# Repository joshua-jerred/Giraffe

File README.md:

# Giraffe <!-- omit from toc -->

### A Unified Flight Command and Control System <!-- omit from toc -->

### [Iteration 0.8](https://giraffe.joshuajer.red/md_docs_Doxygen_pages_versions.html)

---

## Learn More About it

Read about why I'm doing this: [https://joshuajer.red/Giraffe-Introduction/](https://joshuajer.red/Giraffe-Introduction/)

Detailed software documentation (Doxygen): [http://giraffe.joshuajer.red/](http://giraffe.joshuajer.red/)

Check out the [Giraffe GitHub Project](https://github.com/users/joshua-jerred/projects/3) to see what I'm currently working on.

---

## Photos

> 
> The Giraffe Network - A diagram of Giraffe's components and how they interact with each other.

> 
> The web client 'command center' page.

> 
>
> The flight computer prototype 2 PCB on top of a Pi 4. It's accompanied by the SA868 testing PCB with a dummy load antenna and it's supporting PCM2902 sound card testing PCB. Connected with debugging spaghetti.

>  >
> This is the web client, used to configure the flight computer on the ground
> and to monitor/control it in the air.

---

## Table of Contents <!-- omit from toc -->

- [About](#about)
  - [Current High Level Functionality](#current-high-level-functionality)
  - [Planned High Level Functionality Prior to the First Flight](#planned-high-level-functionality-prior-to-the-first-flight)
  - [Development Details](#development-details)
- [Hardware](#hardware)
  - [Hat](#hat)
  - [Shoe](#shoe)
- [Building and Installing the Flight Software](#building-and-installing-the-flight-software)
  - [Installing Prerequisites](#installing-prerequisites)
  - [Building the Flight Software](#building-the-flight-software)
- [Flight Software Configuration/Web Client](#flight-software-configurationweb-client)

---

# About

Giraffe is a "flight command and control system" first developed for high
altitude balloon flights.

The purpose of this project is mainly to have a 'learning lab' where I can experiment with all of the things that I'm interested in. This includes C++, Linux Embedded Development, Circuit Design, RF/Amateur Radio, Node.js, CI, interfacing hardware with the web, meta-programming, and more.

The system includes the following key components:

- **GFS** Giraffe Flight System
  - The hardware and software that actually flies
- **GGS** Giraffe Ground Station
  - Software that helps interface with the flight system both on the ground
    and in the air.
- **GDL** Giraffe Data Link
  - The hardware and software used on both GFS and GGS to connect them together
    via long distance radio links.
- **GWC** Giraffe Web Client
  - A web client to easily configure, control, and monitor all Giraffe
    components in one place.

## Current High Level Functionality

- Detailed configuration via the web interface of all system components.
- Telemetry support for APRS, SSTV, and Data Packets.
- Aggressive error handling for all software components. Everything is designed
  to be able to fail gracefully and recover when possible.
- Detailed and configurable logging of data and telemetry.
- Drivers/Firmware for the Raspberry Pi BCM interface along with many different sensors, radios, and other hardware.

## Planned High Level Functionality Prior to the First Flight

- Two way communication via GDL

## Development Details

The flight software is written in C++, the web interface and ground stations are written in Node.js, and some Python is sprinkled in.

There are common components, including a large collection of configuration
and data point metadata files that are used to generate code for both the
flight system and the ground station. For example, to add a configuration
option for the flight computer, you just need to add the information to the
metadata file, run the generator, rebuild, and redeploy. It will then be inside
of the flight software, configurable via the web interface, and safely
implemented to restrained values to prevent misconfiguration.
This works for integers, floats, strings, and enums.

Being a 'learning lab' project, nearly everything is built from the ground up
including my own implementations of:

- Linux I2C and Serial wrappers
- BCM Interface for direct GPIO control on the Raspberry Pi
- Device Drivers
  - BMP180 (I2C Environmental Sensor)
  - BME280 (I2C Environmental Sensor)
  - SAM-M8Q (I2C GPS using the UBX protocol)
  - SA868 (2w VHF Radio Module)
  - MCP3021 (I2C ADC)
- Modulation (Using my WAV file generation and Modulation library)
  - PSK - For data packets
  - AFSK, AX.25, APRS (Position and Telemetry) - For tracking via aprs.fi
  - SSTV (Robot36) - For image transmission
- A web interface for flight computer debugging, configuration, and control
- Custom hardware for the flight computer
- Simple configuration file for the flight computer

Libraries that I've written for this project:

- [Boost_erSeat, a library with a few useful functions that I use in many different projects](https://github.com/joshua-jerred/Boost_erSeat)
- [WavGen, a .wav File Generator](https://github.com/joshua-jerred/WavGen)
- [MWAV, a library for modulating AFSK, AX.25, APRS, PSK31, and SSTV signals using WavGen](https://github.com/joshua-jerred/MWAV)
- [SSTV Image Tools, a library for overlaying text and getting pixel data for SSTV images](https://github.com/joshua-jerred/SSTV-Image-Tools)

Where I used existing 3rd party libraries:

- JSON parsing for the web server module and configuration reading (nlohmann/json)
- Image Manipulation for PNG/JPEG support in my SSTV Image Tools Library (Magick++)
- Google Test for unit testing

Everything is designed to be modular and extensible so that it can be used for
all types of HAB flights or even some other future implementations where command
and control is needed. The software is made to work on any ARM based single
board computer that runs Linux, like the Raspberry Pi but it is targeted towards
the Pi Zero 2 and Pi 4.

The framework utilizes open communication protocols/modulation modes like APRS,
AFSK, PSK31, and SSTV to allow for easy integration into existing software. Two
way communication, which is currently in development, allows you to send
commands to the flight computer from the ground station. There is a lot more
included that isn't mentioned here, so please see the
[rest of the documentation](http://giraffe.joshuajer.red/).

Too see my more older, simplified, python implementation of this
project check out the [the AOS repo.](https://github.com/joshua-jerred/AOS)

---

# Hardware

I'm currently working on hardware prototypes.

The flight computer is (will be) made up of two boards; it is targeted towards the
Raspberry Pi Zero 2 and maintains the same footprint. The Raspberry Pi will
be sandwiched between the two boards, with the top board being the "hat" and
the bottom board being the "shoe".

## Hat

The hat contains the majority of the circuitry. It is a four layer PCB
containing the following:

- Power Management
  - Connects to the battery (21700 Cells) via a terminal block
  - Includes a 5v linear regulator and support circuitry, this powers the Pi and
    the other PCB
  - Voltage Divider for battery voltage measurement
- Sensors
  - BME280 (Temperature, Pressure, Humidity)
  - MCP3021 (Battery Voltage)
  - CAT24C32 (EEPROM, GPIO Configuration at boot)
  - BMI088 (6 Axis IMU)
- 2x 1-Wire Headers for DS18B20 Temperature Sensors
- 1x I2C Header for general expansion

>  >

> You'll notice a lot of open space on the top of the PCB, this is to isolate
> the SAM-M8Q and to provide it a large ground plane. Although the ground plane
> size is out of spec I have had no issues with acquiring and maintaining a GPS
> lock.

### Known Issues <!-- omit in toc -->

There are a few known issues with prototype 2:

- Power Management! I'm currently working on replacing the linear regulator with
  a boost converter.
- The BME280 is too close to the power supply. This results in much higher
  temperature readings and inaccurate pressure/humidity readings as they're
  temperature compensated.

Other than that, this prototype is working great!

## Shoe

The shoe contains the telemetry circuitry. It is a four layer PCB containing
the following:

- SA868 (2w VHF Radio)
  - Isolation circuitry to prevent interference with the Pi
  - Serial Logic Level Converter (3.3v to 5v)
- Low Pass Filter and SMA Connector
- Integrated PCM2902 Audio Codes
  - USB interface with the Pi
  - 2x input channels, 2x output channels, only one of each is currently used.
- An attempt to impedance match the RF traces from the SA868 to the
  SMA connector and provide shielding.

The radio will be on the very bottom of the hardware stack, hopefully isolating
it from the rest of the hardware.

> Front 

> Back 

### Known Issues <!-- omit in toc -->

- Power control circuitry is not functional. Although 5v power is fully cut off
  with the GPIO controlled optical relay, the SA868 still draw power from
  the serial logic level converter. This results is the SA868 being unreliable
  after restarts and frequency changes. More isolation needs to be added.

### Shoe Testing PCBs <!-- omit in toc -->

I'm just waiting to finish debugging the SA868 and PCM2902 testing PCBs before
ordering this one.

> <p float="left">
> 
> 
> </p>
> Left: SA868 Testing PCB with a dummy load antenna.
>
> Right: PCM2902 Testing PCB with USB interface.

> 
>
> Unfortunately, I don't have the equipment to test it properly, but the SA868
> PCB includes a low pass filter to take care of the messy RF output that these
> modules are known to have.

---

# Building and Installing the Flight Software

## Installing Prerequisites

## Building the Flight Software

```bash
# Clone the repo with it's submodules (MWAV, WAVGen, and SSTV Image Tools)
git clone --recurse-submodules https://github.com/joshua-jerred/Giraffe.git

# If using the --recurse-submodules flag didn't work for any reason, you can use:
# git submodule update --init --recursive --remote
# and then pull the latest change.

# Move into the repo and create a build directory
cd Giraffe && mkdir build && cd build

# Configure the build
cmake .. # You can add -DSSTV_ENABLED=OFF to disable SSTV (Requires Magick++)

# Build the flight system
make giraffe_flight_system

# Install is currently disabled until some details are finalized
# Install the flight system (Optional)
# sudo make install
```

---

# Flight Software Configuration/Web Client

Configuration is no longer done through the config file, but instead through
the web interface! This is where the ground station and flight system are
configured.

Multiple clients can be connected to the web interface at once to allow for a
team to monitor the flight together.

---

Development is no longer done by release, but instead features will be added
as they are completed.

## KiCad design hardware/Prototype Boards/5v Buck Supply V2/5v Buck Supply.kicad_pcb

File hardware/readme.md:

# Giraffe Hardware

- KiCad 7+
- All symbols should be in the `./symbols/` directory
- All footprints should be in the `./footprints/` directory

Slowly moving to a more modular design and better documentation.

## Flight Computer
- ./giraffe_flight_computer/
- ./power_board/

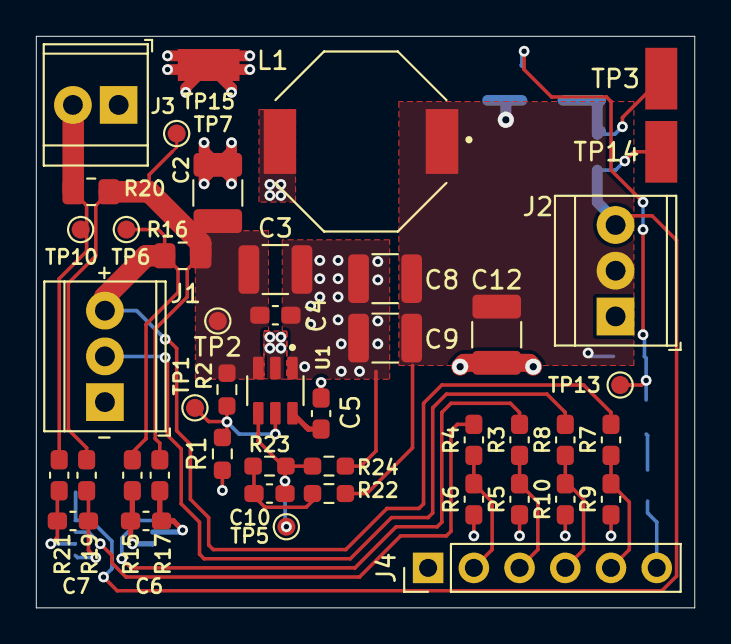
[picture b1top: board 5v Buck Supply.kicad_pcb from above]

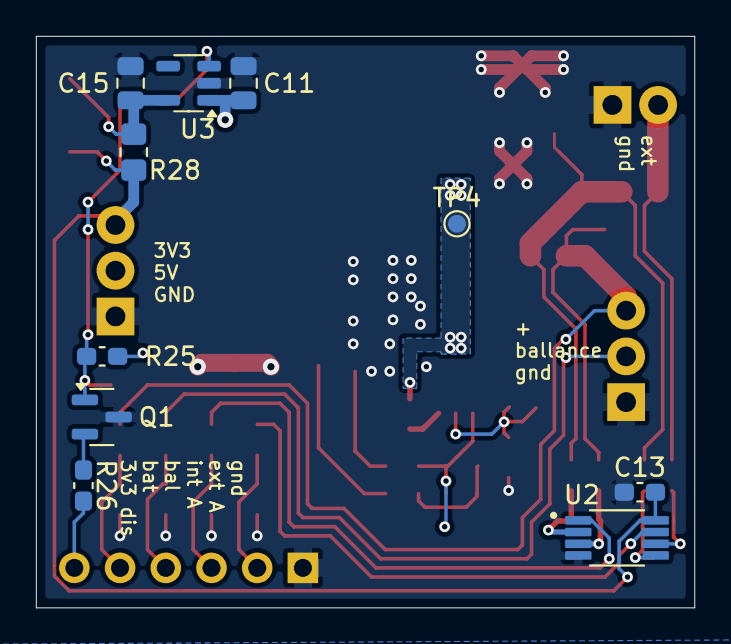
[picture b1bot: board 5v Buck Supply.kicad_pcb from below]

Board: 2 copper layers, 36.6 x 31.8 mm, 55 parts (10 on the bottom side), 26 nets.

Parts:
C2, C12: DNS; C_1210_3225Metric_Pad1.33x2.70mm_HandSolder
C3: 10uf; C_1210_3225Metric
C4, C5, C13: 0.1uf; C_0603_1608Metric_Pad1.08x0.95mm_HandSolder
C6, C7: DNS; C_0603_1608Metric_Pad1.08x0.95mm_HandSolder
C8, C9: 22uf; C_1210_3225Metric
C10: 75pf; C_0603_1608Metric_Pad1.08x0.95mm_HandSolder
C11, C15: 1uf; C_0805_2012Metric
J1: BATT; TerminalBlock_TE_282834-3_1x03_P2.54mm_Horizontal
J2: PRIMARY; TerminalBlock_TE_282834-3_1x03_P2.54mm_Horizontal
J3: EXTERNAL; TerminalBlock_TE_282834-2_1x02_P2.54mm_Horizontal
J4: IO; PinHeader_1x06_P2.54mm_Vertical
L1: 10uH; IND_SRU1048-100Y
Q1: NPN; SOT-23
R1, R2: DNS; R_0603_1608Metric_Pad0.98x0.95mm_HandSolder
R3, R4, R5, R6, R7, R8, R9, R10, R25, R26: R; C_0603_1608Metric_Pad1.08x0.95mm_HandSolder
R15, R17, R19, R21: 0; C_0603_1608Metric_Pad1.08x0.95mm_HandSolder
R16, R20, R28: R; R_0805_2012Metric_Pad1.20x1.40mm_HandSolder
R22: 49.9k; R_0603_1608Metric_Pad0.98x0.95mm_HandSolder
R23: 100k; R_0603_1608Metric_Pad0.98x0.95mm_HandSolder
R24: 13.3k; R_0603_1608Metric_Pad0.98x0.95mm_HandSolder
TP1, TP6, TP7, TP10: TestPoint; TestPoint_Pad_D1.0mm
TP2, TP4, TP5, TP13: TestPoint_Pad_D1.0mm
TP3, TP14, TP15: TestPoint; KEYSTONE_5015
U1: TPS54302DDCR; SOT95P280X110-6N
U2: INA2180Ax; SOP65P490X110-8N
U3: AP2112K-3.3; SOT-23-5

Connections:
3V3 Primary: C13.1, J2.3, R28.2, TP14.1, U2.8 (VS)
3V3_DISABLE: J4.6, R26.2
5V Primary: C8.1, C9.1, C11.1, C12.1, J2.2, L1.1, R22.1, R25.2, U3.1 (VIN)
+BATT: J1.3, R7.1, R15.1, R16.1, TP6.1
+BATT External: J3.2, R20.2, R21.1, TP10.1
+BATT Primary: C2.1, C3.1, C4.1, R2.2, R16.2, R17.1, R19.1, R20.1, TP2.1, TP7.1, U1.3 (VIN)
/3v3_en: Q1.1 (C), R25.1, TP13.1, U3.3 (EN)
/3v3_out: C15.1, R28.1, TP3.1, U3.5 (VOUT)
/adc_scaled:batt: J4.5, R7.2, R9.1
/adc_scaled:batt_ballance: J4.4, R8.2, R10.1
/adc_scaled:current_batt: J4.3, R3.2, R5.1
/adc_scaled:current_external: J4.2, R4.2, R6.1
/batt_ext+: C7.2, R19.2, U2.5 (IN+2)
/batt_ext-: C7.1, R21.2, U2.6 (IN-2)
/batt_primary+: C6.2, R15.2, U2.3 (IN+1)
/batt_primary-: C6.1, R17.2, U2.2 (IN-1)
/buck_boot: C5.1, U1.6 (BOOT)
/buck_enable: R1.2, R2.1, TP1.1, U1.5 (EN)
/buck_feedback: C10.2, R23.2, R24.1, TP5.1, U1.4 (FB)
/buck_sw: C5.2, L1.2, TP4.1, U1.2 (SW)
GND: C2.2, C3.2, C4.2, C8.2, C9.2, C11.2, C12.2, C13.2, C15.2, J1.1, J2.1, J3.1, J4.1, Q1.3 (E), R1.1, R5.2, R6.2, R9.2, R10.2, R24.2, TP15.1, U1.1 (GND), U2.4 (GND), U3.2 (GND)
unnamed: C10.1, R22.2, R23.1
unnamed: Q1.2 (B), R26.1
batt_ballance: J1.2, R8.1
current_sense_batt: R3.1, U2.1 (OUT1)
current_sense_external: R4.1, U2.7 (OUT2)

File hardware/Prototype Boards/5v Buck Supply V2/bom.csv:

"Reference","Value","Footprint","Qty","DNP"
"BAT_CON1","BAT","","1","DNP"
"C2,C12,R1,R2","DNS","-- mixed values --","4","DNP"
"C3","10uf","Capacitor_SMD:C_1210_3225Metric","1",""
"C4,C5,C13","0.1uf","Capacitor_SMD:C_0603_1608Metric_Pad1.08x0.95mm_HandSolder","3",""
"C6,C7","C","Capacitor_SMD:C_0603_1608Metric_Pad1.08x0.95mm_HandSolder","2",""
"C8,C9","22uf","Capacitor_SMD:C_1210_3225Metric","2",""
"C10","75pf","Capacitor_SMD:C_0603_1608Metric_Pad1.08x0.95mm_HandSolder","1",""
"C11,C15","1uf","Capacitor_SMD:C_0805_2012Metric","2",""
"J1","BATT","TerminalBlock_TE-Connectivity:TerminalBlock_TE_282834-3_1x03_P2.54mm_Horizontal","1",""
"J2","PRIMARY","TerminalBlock_TE-Connectivity:TerminalBlock_TE_282834-3_1x03_P2.54mm_Horizontal","1",""
"J3","EXTERNAL","TerminalBlock_TE-Connectivity:TerminalBlock_TE_282834-2_1x02_P2.54mm_Horizontal","1",""
"J4","IO","Connector_PinHeader_2.54mm:PinHeader_1x06_P2.54mm_Vertical","1",""
"L1","10uH","footprints:IND_SRU1048-100Y","1",""
"Q1","NPN","Package_TO_SOT_SMD:SOT-23","1",""
"R3,R4,R5,R6,R7,R8,R9,R10,R15,R16,R17,R19,R20,R21,R25,R26,R28","R","-- mixed values --","17",""
"R22","49.9k","Resistor_SMD:R_0603_1608Metric_Pad0.98x0.95mm_HandSolder","1",""
"R23","100k","Resistor_SMD:R_0603_1608Metric_Pad0.98x0.95mm_HandSolder","1",""
"R24","13.3k","Resistor_SMD:R_0603_1608Metric_Pad0.98x0.95mm_HandSolder","1",""
"TP1,TP3,TP6,TP7,TP10,TP14,TP15","TestPoint","-- mixed values --","7",""
"TP2,TP4,TP5,TP13","~","TestPoint:TestPoint_Pad_D1.0mm","4",""
"U1","TPS54302DDCR","footprints:SOT95P280X110-6N","1",""
"U2","INA2180Ax","footprints:SOP65P490X110-8N","1",""
"U3","AP2112K-3.3","Package_TO_SOT_SMD:SOT-23-5","1",""

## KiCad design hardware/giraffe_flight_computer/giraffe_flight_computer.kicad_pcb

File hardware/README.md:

Currently in the prototyping stage, nothing here should be used as reference.

Some footprints are from SnapEDA so they could not be included due to license restrictions.

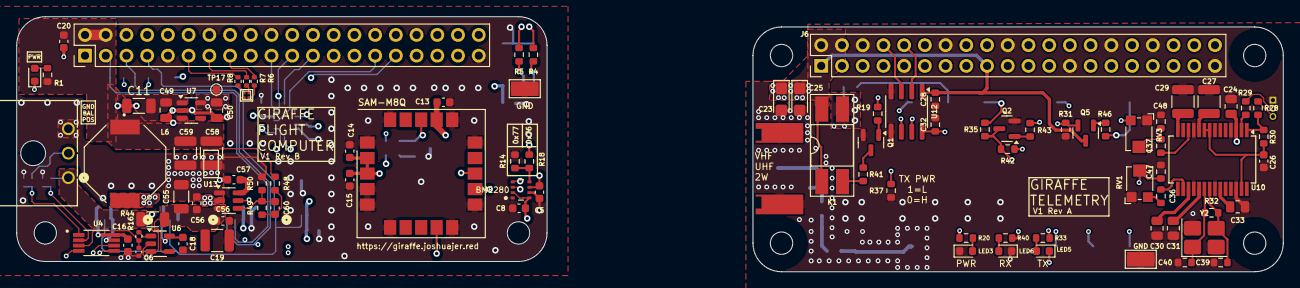
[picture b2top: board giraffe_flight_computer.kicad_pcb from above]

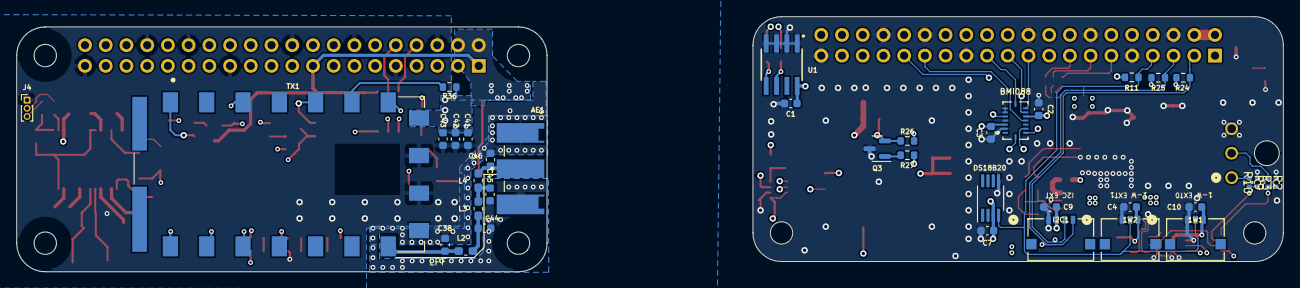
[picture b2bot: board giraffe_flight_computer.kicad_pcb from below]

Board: 4 copper layers, 155.2 x 31.3 mm, 129 parts (37 on the bottom side), 84 nets.

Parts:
1W1: 1W1; CONN_5037630000-SD_03_MOL
1W2: 1W2; CONN_5037630000-SD_03_MOL
AE1: ANT; MolexSmaConnector
C1, C2, C3, C4, C5, C7, C8, C9, C10, C13, C14, C15, C16, C18, C20, C41, C56, C56#2, C57: 0.1µF; C_0603_1608Metric
C6: C_Small; C_0402_1005Metric
C11: 10uf; C_1206_3216Metric
C19, C58, C59: 22µF; C_1210_3225Metric
C23, C25: 10μF; CP_EIA-3216-18_Kemet-A
C24, C31, C33: 1μF; R_0805_2012Metric
C26: 1μF; C_0603_1608Metric
C27, C29: 10μF; R_1210_3225Metric
C28, C32, C39, C40: 0.1μF; R_0603_1608Metric
C30: 1uF; R_0805_2012Metric
C36, C37: 1μF; R_0603_1608Metric
C38, C46: 20pF; C_0603_1608Metric
C42: 10kpF; C_0603_1608Metric
C43: 1kpF; C_0603_1608Metric
C44, C45: 36pF; C_0603_1608Metric
C47, C48: ?; R_0603_1608Metric
C49, C50: 1uf; C_0805_2012Metric
C55: 10µF; C_1206_3216Metric
C60: 75pf; C_0603_1608Metric
GND: GND; TestPoint_Keystone_5015_Micro-Minature
I2C1: I²C; CONN_5037630000-SD_04_MOL
J1: PI; pi_zero
J4: USB; PinHeader_1x03_P1.00mm_Vertical
J6: PI; SHOE_PCB
J7: Conn_01x03; CONN_SD-43650-001_03_MOL
K1: TLP241A; DIP-4_W8.89mm_SMDSocket_LongPads
L2, L4: 56nH; L_0603_1608Metric_Pad1.05x0.95mm_HandSolder
L3: 68nH; L_0603_1608Metric_Pad1.05x0.95mm_HandSolder
L6: 10uH; IND_SRU1048-100Y
LED1: SML-D12M8WT86; LED_0603_1608Metric
LED2: B36S3RGB-F6C0001HOU1930; B36S3RGB LED
LED3: PWR; LED_0603_1608Metric
LED5, LED6: LED_0603_1608Metric
Q1, Q2, Q5: BC847CT; SOT-23
Q3: NPN; SOT-23
R1: 56Ω; R_0603_1608Metric
R2, R3: ?; R_0402_1005Metric
R4, R5: 3.9kΩ; R_0603_1608Metric
R6: 270Ω; R_0402_1005Metric
R7, R8: 360Ω; R_0402_1005Metric
R9: 6.8k; R_0402_1005Metric
R10: 2.2k; R_0402_1005Metric
R11: 4.7kΩ; R_0603_1608Metric
R14, R18, R35, R36, R37: 0Ω; R_0603_1608Metric
R16: R_Small; R_0402_1005Metric
R19, R43: 50kΩ; R_0603_1608Metric
R20, R33: 150Ω; R_0603_1608Metric
R24, R25: *; R_0603_1608Metric
R26, R27: ?Ω; R_0603_1608Metric
R28, R29: 22Ω; R_0603_1608Metric
R30: 1.5kΩ; R_0603_1608Metric
R31, R42, R46: 5kΩ; R_0603_1608Metric
R32: 1MΩ; R_0603_1608Metric
R40: ?kΩ; R_0603_1608Metric
R41: 470Ω; R_0603_1608Metric
R44: 0.01Ω; R_1206_3216Metric
R48: 49; R_0603_1608Metric
R49: 100k; R_0603_1608Metric
R50: 13.3k; R_0603_1608Metric
RV1, RV3: 100k; Potentiometer_Bourns_TC33X_Vertical
TP3: GND; TestPoint_Keystone_5015_Micro-Minature
TP17: TestPoint; TestPoint_Pad_D1.0mm
TX1: SA868; DORJI_DRA818V
U1: CAT24C32; CAT24C32WI_GT3
U2: BMI088
U3: DS18B20; MSOP-8_3x3mm_P0.65mm
U4: MAX11613; SOP65P490X110-8N
U5: BME280
U6: INA180A3; SOT-23-5
U7: TLV75533PDBV; SOT-23-5
U8: SAM-M8Q; ublox_SAM-M8Q
U10: PCM2902C; SSOP-28_5.3x10.2mm_P0.65mm
U12: ISO6720B; SOIC-8_3.9x4.9mm_P1.27mm
U13: TPS54302; SOT-23-6
Y2: 12 MHz; Crystal_SMD_3225-4Pin_3.2x2.5mm_HandSoldering

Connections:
/hat/1_WIRE: 1W1.2, 1W2.2, J1.7 (GCLK0/GPIO4), R11.2, U3.4 (DQ)
/hat/+BATT: J7.1, R9.1, R44.1, U6.3 (+)
/hat/ADC.CH0: R2.2, R3.1, U4.1 (AIN0)
/hat/ADC.CH1: R9.2, R10.1, U4.2 (AIN1)
/hat/ADC.CH2: C6.1, R16.2, U4.3 (AIN2)
/hat/BAT_BALANCE: J7.2, R2.1
/hat/BAT_SENSED: C19.1, C55.1, C56.1, C56#2.1, R44.2, U6.4 (-), U13.3 (VIN)
/hat/BMI088.INT1: J1.31 (GCLK2/GPIO6), U2.16 (INT1)
/hat/BMI088.INT3: J1.29 (GCLK1/GPIO5), U2.12 (INT3)
/hat/EEPROM.SCL: J1.28 (ID_SC/GPIO1), R5.1, U1.6 (SCL)
/hat/EEPROM.SDA: J1.27 (ID_SD/GPIO0), R4.1, U1.5 (SDA)
/hat/I2C0.SCL: I2C1.4, J1.5 (SCL/GPIO3), R25.2, U4.5 (SCL), U5.4 (SCK), U8.12 (SCL)
/hat/I2C0.SDA: I2C1.3, J1.3 (SDA/GPIO2), R24.1, U4.6 (SDA), U5.3 (SDI), U8.9 (SDA)
/hat/SAM_M8Q.RST: J1.32 (PWM0/GPIO12), R27.2
/hat/SAM_M8Q.TX_RDY: J1.33 (PWM1/GPIO13), U8.13 (TXD)
/hat/SPI0.CE0: J1.24 (~CE0/GPIO8), U2.14 (CSB1)
/hat/SPI0.CE1: J1.26 (~CE1/GPIO7), U2.5 (CSB2)
/hat/SPI0.MISO: J1.21 (MISO0/GPIO9), U2.10 (SDO2), U2.15 (SDO1)
/hat/SPI0.MOSI: J1.19 (MOSI0/GPIO10), U2.9 (SDA/SDI)
/hat/SPI0.SCLK: J1.23 (SCLK0/GPIO11), U2.8 (SCL/SCK)
/hat/STATUS_LED.BLUE: J1.11 (GPIO17), R8.1
/hat/STATUS_LED.GREEN: J1.13 (GPIO27), R7.1
/hat/STATUS_LED.RED: J1.15 (GPIO22), R6.1
/shoe/AUDIO_IN_LEFT: C37.2, C48.1, RV3.2
/shoe/PI_GPIO_SA868_PTT: J6.18 (GPIO24), R43.1
/shoe/PI_GPIO_SA868_RX: J6.22 (GPIO25), Q5.2 (E), R31.1, R40.2
/shoe/PI_GPIO_SHOE_POWER_CONTROL: J6.16 (GPIO23), R19.1
/shoe/SA868 AUDIO_OUT: RV3.3, TX1.3 (AF_OUT)
/shoe/SA868 H/L: R37.2, TX1.7 (H/L)
/shoe/SA868 MIC_IN: C47.1, RV1.2, TX1.18 (MIC_IN)
/shoe/SA868 PTT: R35.2, TX1.5 (PTT)
/shoe/SA868 RF: C38.1, L2.1, TX1.12 (ANT)
/shoe/SA868 RX: R46.1, TX1.1 (SQ)
/shoe/SA868 UART RXD: TX1.16 (RXD), U12.6 (OUTB)
/shoe/SA868 UART TXD: TX1.17 (TXD), U12.7 (INA)
/shoe/S_5V_IN: C23.1, C25.1, J6.2 (5V), J6.4 (5V), K1.1 (Anode), K1.4 (Drain)
/shoe/UART.RX: J6.10 (GPIO15/RXD), U12.2 (OUTA)
/shoe/UART.TX: J6.8 (GPIO14/TXD), U12.3 (INB)
/shoe/USB Audio Codec/audio_codec_out_left: C36.2, RV1.3
H_3V3: 1W1.3, 1W2.3, C1.1, C2.2, C3.2, C4.2, C5.2, C7.2, C8.2, C9.2, C10.2, C13.1, C14.1, C15.1, C16.1, C18.1, C50.2, I2C1.2, R4.2, R5.2, R11.1, R18.2, R24.2, R25.1, R26.2, TP17.1, U1.8 (VCC), U2.3 (VDD), U2.11 (VDDIO), U3.3 (V_{DD}), U4.8 (Vdd), U5.2 (CSB), U5.6 (VDDIO), U5.8 (VDD), U6.5 (V+), U7.5 (OUT), U8.2 (VCC_IO), U8.3 (V_BCKP), U8.17 (VCC)
H_5V: C11.2, C20.2, C49.2, C58.1, C59.1, J1.2 (5V), J1.4 (5V), L6.1, R1.1, R48.1, U7.1 (IN), U7.3 (EN)
H_GND: 1W1.1, 1W2.1, C1.2, C2.1, C3.1, C4.1, C5.1, C6.2, C7.1, C8.1, C9.1, C10.1, C11.1, C13.2, C14.2, C15.2, C16.2, C18.2, C19.2, C20.1, C49.1, C50.1, C55.2, C56.2, C56#2.2, C58.2, C59.2, I2C1.1, J1.6 (GND), J1.9 (GND), J1.14 (GND), J1.20 (GND), J1.25 (GND), J1.30 (GND), J1.34 (GND), J1.39 (GND), J7.3, LED1.1 (K), LED2.4 (K), Q3.3 (E), R3.2, R10.2, R14.2, R50.2, TP3.1, U1.1 (A0), U1.2 (A1), U1.3 (A2), U1.4 (VSS), U2.2 (NC), U2.4 (GNDA), U2.6 (GNDIO), U2.7 (PS), U3.5 (GND), U4.7 (GND), U5.1 (GND), U5.7 (GND), U6.2 (GND), U7.2 (GND), U8.1 (GND), U8.4 (GND), U8.5 (GND), U8.6 (GND), U8.10 (GND), U8.11 (GND), U8.15 (GND), U8.16 (GND), U8.20 (GND), U13.1 (GND)
unnamed: AE1.1 (A), C46.1, L4.2
unnamed: C44.1, L2.2, L3.1
unnamed: C45.1, L3.2, L4.1
unnamed: C60.1, R48.2, R49.1
unnamed: J4.2, R29.1
unnamed: J4.3, R28.1
unnamed: K1.2 (Cathode), R41.1
unnamed: LED1.2 (A), R1.2
unnamed: LED2.3 (BA), R8.2
unnamed: LED2.2 (GA), R7.2
unnamed: LED2.1 (RA), R6.2
unnamed: LED3.2 (A), R20.2
unnamed: LED5.2 (A), R33.1
unnamed: LED5.1 (K), Q2.3 (C), R35.1, R42.2
unnamed: LED6.2 (A), R40.1
unnamed: Q1.1 (B), R19.2
unnamed: Q1.3 (C), R41.2
unnamed: Q2.1 (B), R43.2
unnamed: Q3.1 (B), R27.1
unnamed: Q3.2 (C), R26.1, U8.18 (~RESET)
unnamed: Q5.1 (B), R46.2
unnamed: R16.1, U6.1
unnamed: R36.1, TX1.6 (PD)
unnamed: R14.1, R18.1, U5.5 (SDO)
unnamed: R28.2, R30.2, U10.1 (D+)
unnamed: R29.2, U10.2 (D-)
unnamed: C26.2, R30.1, U10.8 (SEL0), U10.9 (SEL1), U10.27 (VDDI)
unnamed: C27.1, U10.10 (VCCCI)
unnamed: C30.2, U10.17 (VCCP1I)
unnamed: C31.2, U10.19 (VCCP2I)
unnamed: C33.2, U10.23 (VCCXI)
unnamed: C29.1, U10.14 (VCOM)
unnamed: C37.1, U10.12 (VINL)
unnamed: C36.1, U10.16 (VOUTL)
unnamed: C39.1, R32.2, U10.21 (XTI), Y2.3
unnamed: C40.1, R32.1, U10.20 (XTO), Y2.1
unnamed: C57.1, U13.6 (BOOT)
unnamed: C60.2, R49.2, R50.1, U13.4 (FB)
unnamed: C57.2, L6.2, U13.2 (SW)
S_3V3: C28.2, J6.1 (3V3), J6.17 (3V3), Q5.3 (C), U12.1 (VCC1)
S_5V: C24.1, C32.1, C41.2, C42.2, C43.2, K1.3 (Drain), R20.1, R33.2, R36.2, R42.1, TX1.8 (VBAT), U10.3 (VBUS), U12.8 (VCC2)
S_GND: AE1.2 (Shield), AE1.3 (Shield), AE1.4 (Shield), AE1.5 (Shield), C23.2, C24.2, C25.2, C26.1, C27.2, C28.1, C29.2, C30.1, C31.1, C32.2, C33.1, C38.2, C39.2, C40.2, C41.1, C42.1, C43.1, C44.2, C45.2, C46.2, C47.2, C48.2, GND.1, J4.1, J6.6 (GND), J6.9 (GND), J6.14 (GND), J6.20 (GND), J6.25 (GND), J6.30 (GND), J6.34 (GND), J6.39 (GND), LED3.1 (K), LED6.1 (K), Q1.2 (E), Q2.2 (E), R31.2, R37.1, RV1.1, RV3.1, TX1.9 (GND), TX1.10 (GND), U10.4 (DGNDU), U10.11 (AGNDC), U10.18 (AGNDP), U10.22 (AGNDX), U10.26 (DGND), U12.4 (GND1), U12.5 (GND2), Y2.2, Y2.4

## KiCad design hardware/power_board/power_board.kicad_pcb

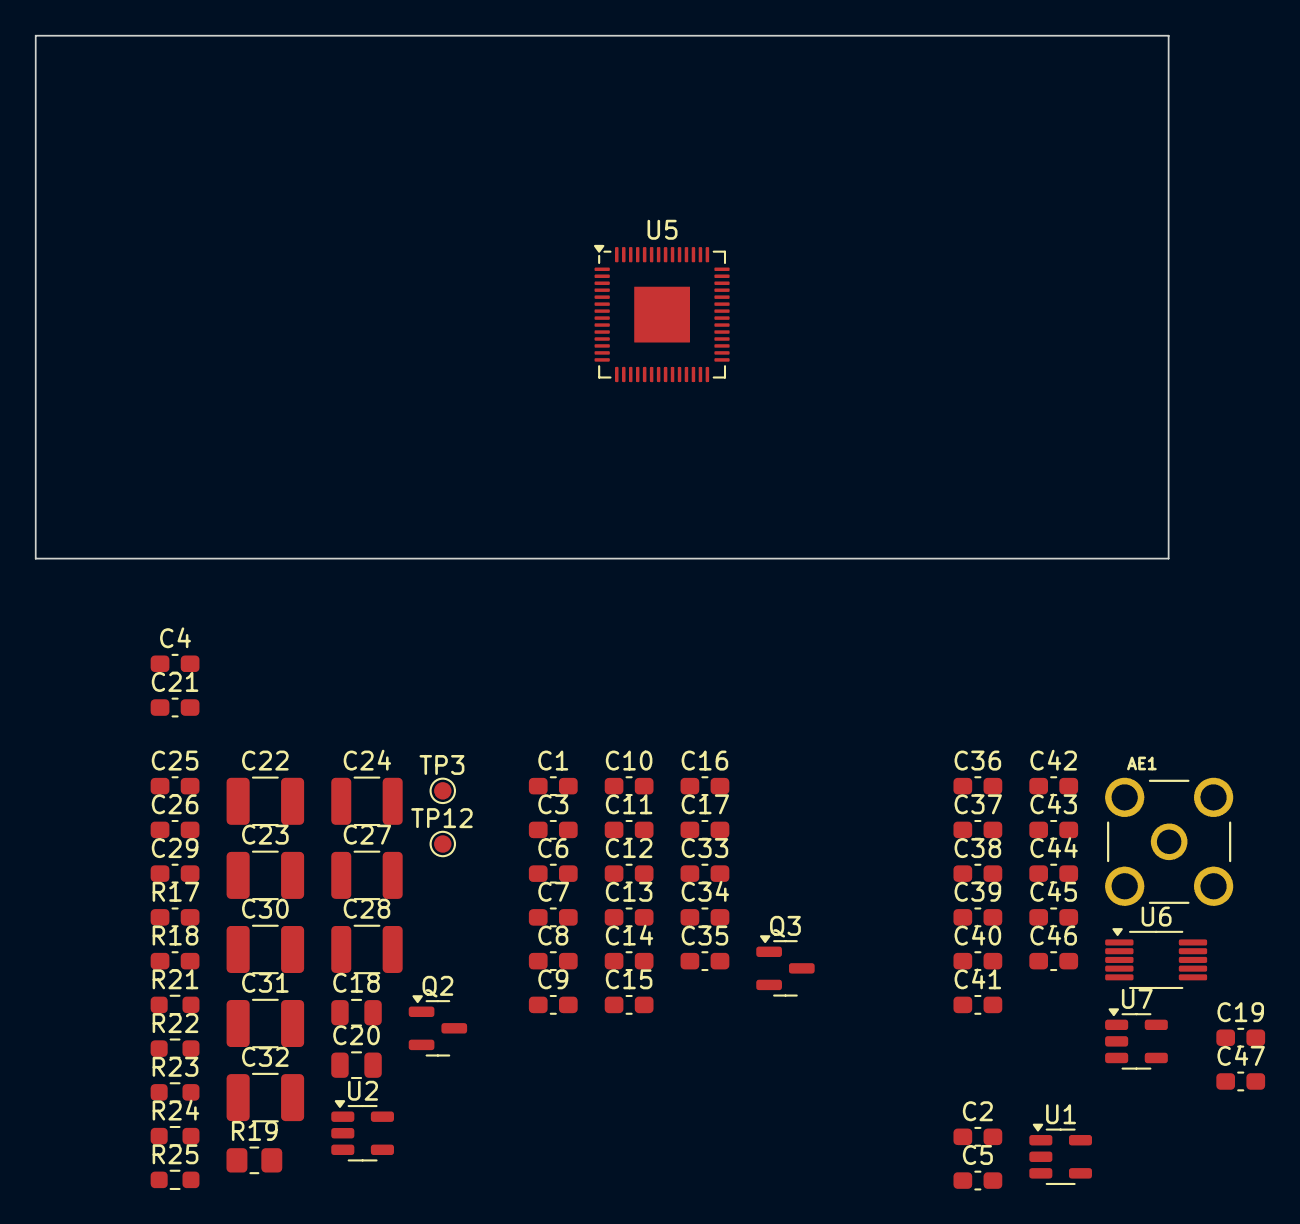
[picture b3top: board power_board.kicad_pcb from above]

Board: 4 copper layers, 65.0 x 30.0 mm, 65 parts (0 on the bottom side), 26 nets, no tracks yet.

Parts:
AE1: LINX_CONSMA001-G
C1, C3: 15pf; C_0603_1608Metric_Pad1.08x0.95mm_HandSolder
C2, C6, C7, C8, C9, C10, C11, C14, C15, C19, C25, C26, C35, C36, C37: 0.1uf; C_0603_1608Metric_Pad1.08x0.95mm_HandSolder
C4, C5, C21, C40, C42, C43, C44, C45: ?; C_0603_1608Metric_Pad1.08x0.95mm_HandSolder
C12, C13, C33, C41, C46: 1uf; C_0603_1608Metric_Pad1.08x0.95mm_HandSolder
C16, C17: DNS; C_0603_1608Metric_Pad1.08x0.95mm_HandSolder
C18, C20: 1uf; C_0805_2012Metric
C22, C23, C30, C31, C32: DNS; C_1210_3225Metric_Pad1.33x2.70mm_HandSolder
C24: 10uf; C_1210_3225Metric
C27, C28: 22uf; C_1210_3225Metric
C29: 75pf; C_0603_1608Metric_Pad1.08x0.95mm_HandSolder
C34: 10uf; C_0603_1608Metric_Pad1.08x0.95mm_HandSolder
C38, C39: ?pf; C_0603_1608Metric_Pad1.08x0.95mm_HandSolder
C47: 2.2uf; C_0603_1608Metric_Pad1.08x0.95mm_HandSolder
Q2: MMBT3904LT1G; SOT-23
Q3: BC847CT; SOT-23
R17: 10k; C_0603_1608Metric_Pad1.08x0.95mm_HandSolder
R18: 1k; C_0603_1608Metric_Pad1.08x0.95mm_HandSolder
R19: 0; R_0805_2012Metric_Pad1.20x1.40mm_HandSolder
R21, R22: DNS; R_0603_1608Metric_Pad0.98x0.95mm_HandSolder
R23: 49; R_0603_1608Metric_Pad0.98x0.95mm_HandSolder
R24: 100k; R_0603_1608Metric_Pad0.98x0.95mm_HandSolder
R25: 13.3k; R_0603_1608Metric_Pad0.98x0.95mm_HandSolder
TP3, TP12: TestPoint; TestPoint_Pad_D1.0mm
U1: INA180A; SOT-23-5
U2: AP2112K-3.3; SOT-23-5
U5: RP2040; QFN-56-1EP_7x7mm_P0.4mm_EP3.2x3.2mm
U6: Si5351A-B-GT; MSOP-10_3x3mm_P0.5mm
U7: MIC2091-2YM5; SOT-23-5

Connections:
3V3_PICO: C6.2, C7.2, C8.2, C9.2, C10.2, C11.2, C12.2, C19.2, C33.2, C34.2, C35.2, C41.2, C46.2, C47.2, U5.1 (IOVDD), U5.10 (IOVDD), U5.22 (IOVDD), U5.33 (IOVDD), U5.42 (IOVDD), U5.43 (ADC_AVDD), U5.44 (VREG_IN), U5.48 (USB_VDD), U5.49 (IOVDD), U7.1 (VIN)
5V Primary: C18.1, R17.2, U2.1 (VIN)
5V_PRIMARY: C27.1, C28.1, C30.1, C31.1, C32.1, R23.1
+3V3_RP2040: C2.1, U1.5 (VS)
/Main Power Supply/3v3_en: Q2.1 (C), R17.1, TP3.1, U2.3 (EN)
/Main Power Supply/3v3_out: C20.1, R19.1, U2.5 (VOUT)
/Main Power Supply/+BATT_FILTERED: C22.1, C23.1, C24.1, C25.1, R21.2
/Main Power Supply/buck_enable: R21.1, R22.2, TP12.1
/Main Power Supply/buck_feedback: C29.2, R24.2, R25.1
/Power Input/battery_voltage_signal: C16.2, U5.40 (GPIO28_ADC2)
/Power Input/input_current_sense_signal: C17.2, U1.1 (OUT), U5.41 (GPIO29_ADC3)
/RP2040/2040_I2C0_WSPR.SCL: U5.16 (GPIO13), U6.4 (SCL)
/RP2040/2040_I2C0_WSPR.SDA: U5.15 (GPIO12), U6.5 (SDA)
/RP2040/+1V1_PICO_ADC_REF: C13.2, C14.2, C15.2, U5.23 (DVDD), U5.45 (VREG_VOUT), U5.50 (DVDD)
/RP2040/WSPR Transmitter/Si5351_3V3: C36.2, C37.2, U6.1 (VDD), U6.7 (VDDO), U7.5 (VOUT)
GND: C1.2, C2.2, C3.2, C6.1, C7.1, C8.1, C9.1, C10.1, C11.1, C12.1, C13.1, C14.1, C15.1, C16.1, C17.1, C18.2, C19.1, C20.2, C22.2, C23.2, C24.2, C25.2, C27.2, C28.2, C30.2, C31.2, C32.2, C33.1, C34.1, C35.1, C36.1, C37.1, C38.1, C39.1, C41.1, C42.1, C43.1, C44.1, C45.1, C46.1, C47.1, Q2.3 (E), Q3.2 (E), R22.1, R25.2, U1.2 (GND), U2.2 (GND), U5.19 (TESTEN), U5.57 (GND), U6.8 (GND), U7.2 (GND)
unnamed: AE1.1 (A), C45.2
unnamed: C29.1, R23.2, R24.1
unnamed: C40.1, C42.2
unnamed: Q2.2 (B), R18.1
unnamed: C5.2, U1.3 (IN+)
unnamed: C5.1, U1.4 (IN-)
unnamed: C1.1, U5.20 (XIN)
unnamed: C40.2, U6.10 (CLK0)
unnamed: C38.2, U6.2 (XA)
unnamed: C39.2, U6.3 (XB)

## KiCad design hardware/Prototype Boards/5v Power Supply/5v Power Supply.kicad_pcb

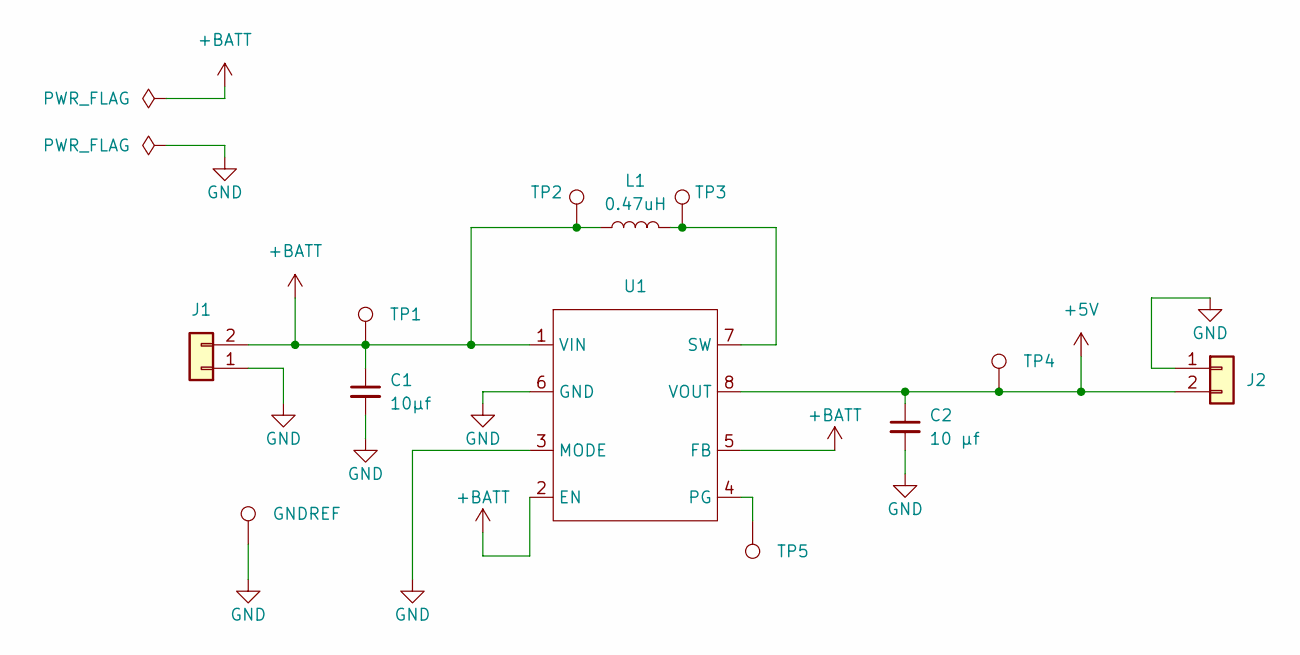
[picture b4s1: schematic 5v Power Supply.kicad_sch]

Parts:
C1: 10μf; C_1210_3225Metric
C2: 10 μf; C_1210_3225Metric
GNDREF: TestPoint_Keystone_5019_Miniature
J1, J2: PinHeader_1x02_P2.54mm_Vertical
L1: 0.47uH; L_Coilcraft_XAL4020-XXX
TP1, TP2, TP3, TP4, TP5: TestPoint_Pad_D1.0mm
U1: SOT-583-8

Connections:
+5V: C2.1, J2.2, TP4.1, U1.8 (VOUT)
+BATT: C1.1, J1.2, L1.1, TP1.1, TP2.1, U1.1 (VIN), U1.2 (EN), U1.5 (FB)
GND: C1.2, C2.2, GNDREF.1, J1.1, J2.1, U1.3 (MODE), U1.6 (GND); also elsewhere on the board
unnamed: TP5.1, U1.4 (PG)
unnamed: L1.2, TP3.1, U1.7 (SW)

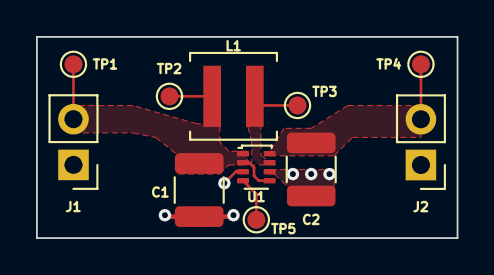
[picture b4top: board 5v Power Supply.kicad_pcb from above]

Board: 2 copper layers, 23.4 x 11.2 mm, 12 parts (1 on the bottom side), 5 nets.

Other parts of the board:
GND: TestPoint_Keystone_5019_Miniature

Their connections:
GND: GND.1; also elsewhere on the board

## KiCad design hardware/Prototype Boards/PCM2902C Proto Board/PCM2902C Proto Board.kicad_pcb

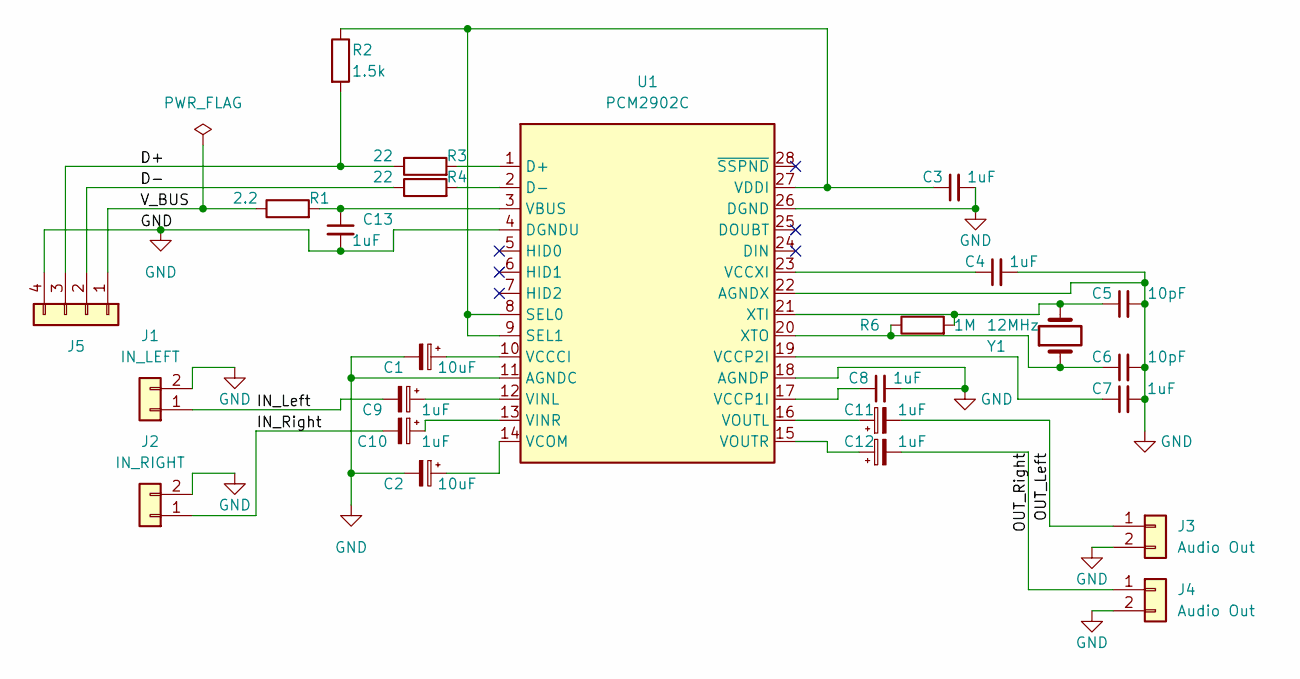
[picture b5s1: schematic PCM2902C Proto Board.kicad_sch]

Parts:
C1, C2: 10uF; C_1210_3225Metric_Pad1.33x2.70mm_HandSolder
C3, C4, C7, C8, C9, C10, C11, C12, C13: 1uF; C_0805_2012Metric_Pad1.18x1.45mm_HandSolder
C5, C6: 10pF; C_0603_1608Metric_Pad1.08x0.95mm_HandSolder
J1: IN_LEFT; PinHeader_1x02_P2.54mm_Vertical; Digikey N/A
J2: IN_RIGHT; PinHeader_1x02_P2.54mm_Vertical; Digikey N/A
J3, J4: Audio Out; PinHeader_1x02_P2.54mm_Vertical; Digikey N/A
J5: USB; PinHeader_1x04_P2.54mm_Vertical; Digikey N/A
R1: 2.2; C_0603_1608Metric_Pad1.08x0.95mm_HandSolder
R2: 1.5k; C_0603_1608Metric_Pad1.08x0.95mm_HandSolder
R3, R4: 22; C_0603_1608Metric_Pad1.08x0.95mm_HandSolder
R6: 1M; C_0603_1608Metric_Pad1.08x0.95mm_HandSolder
U1: PCM2902C; SSOP-28_5.3x10.2mm_P0.65mm; Digikey TI
Y1: 12MHz; Crystal_SMD_HC49-SD_HandSoldering

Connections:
/D+: J5.3, R2.2, R3.1
/D-: J5.2, R4.1
/IN_Left: C9.2, J1.1
/IN_Right: C10.2, J2.1
/OUT_Left: C11.2, J3.1
/OUT_Right: C12.2, J4.1
/V_BUS: J5.1, R1.1
GND: C1.2, C2.2, C3.2, C4.2, C5.2, C6.2, C7.2, C8.2, C13.2, J1.2, J2.2, J3.2, J4.2, J5.4, U1.4 (DGNDU), U1.11 (AGNDC), U1.18 (AGNDP), U1.22 (AGNDX), U1.26 (DGND)
unnamed: C1.1, U1.10 (VCCCI)
unnamed: C2.1, U1.14 (VCOM)
unnamed: C3.1, R2.1, U1.8 (SEL0), U1.9 (SEL1), U1.27 (VDDI)
unnamed: C4.1, U1.23 (VCCXI)
unnamed: C5.1, R6.2, U1.21 (XTI), Y1.2
unnamed: C6.1, R6.1, U1.20 (XTO), Y1.1
unnamed: C7.1, U1.19 (VCCP2I)
unnamed: C8.1, U1.17 (VCCP1I)
unnamed: C9.1, U1.12 (VINL)
unnamed: C10.1, U1.13 (VINR)
unnamed: C11.1, U1.16 (VOUTL)
unnamed: C12.1, U1.15 (VOUTR)
unnamed: C13.1, R1.2, U1.3 (VBUS)
unnamed: R3.2, U1.1 (D+)
unnamed: R4.2, U1.2 (D-)

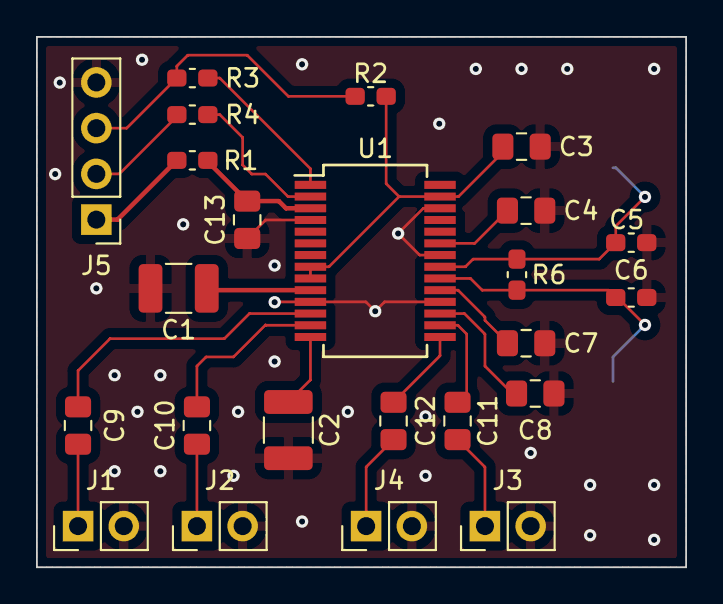
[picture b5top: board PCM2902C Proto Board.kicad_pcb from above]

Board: 2 copper layers, 36.1 x 29.5 mm, 25 parts (1 on the bottom side), 23 nets.
